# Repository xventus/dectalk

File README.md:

# DECTALK 

DECTALK is a simple application of Epson's S1V30120 chip. The communication is controlled by the ESP32 module. Esp32 provides HTTP and serial access for control. MIKROE produces a suitable module carrying the S1V30120 and an amplifier. 

The hardware directory contains a schematic and a board of plenum connections in KICAD format.
The src directory contains the source code for ESP32.

# How to use it 

The module can communicate using HTTP protocol via WiFi or using a serial link.

WiFi connection:
	- on first run, create an AP named `DECTALK CONFIG` or press reset (EN) twice within 5 seconds. 
	- web browser http://192.168.4.100 and fill in the web form

 	POST via build in fomular:  http://192.168.2.220/talk
 	POST via build in fomular:  http://192.168.2.220
	GET with url encoded string as param:   http://XXX.XXX.XXX.XXX/talk?talk=hello%20world

Serial line connection:
	- 9600.8.N.1 

LED status on the ESP32 module:
 - fast LED blinking - error, more detail after serial line
 - slow blinking LED - runs as AP `DECTALK CONFIG`
 - turns on and then off - when playing a message

# Device limitations

The message length is limited to 248 characters.

# Documentation 

S1V30120 module:  https://www.mikroe.com/text-to-speech-click.

S1V30120 initialization data: https://global.epson.com/products_and_drivers/semicon/products/speech/voice/sla/s1v30120_init_data.html

S1V30120 protocol: https://global.epson.com/products_and_drivers/semicon/pdf/id001875.pdf

# Screens

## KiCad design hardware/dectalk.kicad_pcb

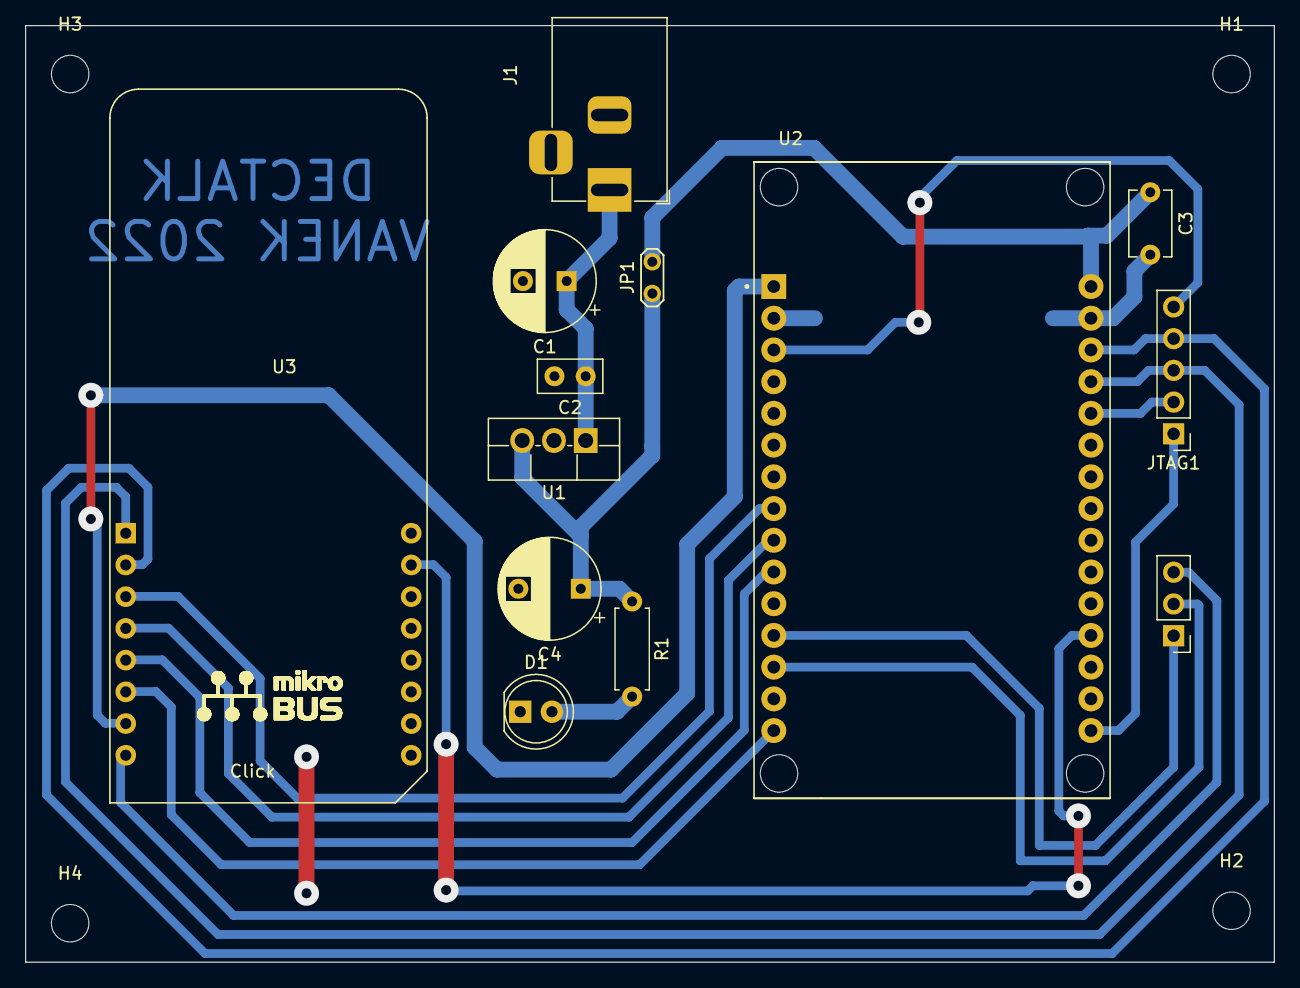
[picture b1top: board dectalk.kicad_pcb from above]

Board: 2 copper layers, 100.0 x 75.0 mm, 17 parts (0 on the bottom side), 18 nets.

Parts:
C1: 1uF; CP_Radial_D8.0mm_P3.50mm
C2: 100nF; C_Disc_D5.0mm_W2.5mm_P2.50mm
C3: 100nF; C_Disc_D5.1mm_W3.2mm_P5.00mm
C4: 10uF; CP_Radial_D8.0mm_P5.00mm
D1: LED; LED_D5.0mm_IRGrey
H1, H2, H3, H4: MountingHole; MountingHole_3mm
J1: Barrel_Jack; BarrelJack_Horizontal
J2: Conn_01x03_Female; PinHeader_1x03_P2.54mm_Vertical
JP1: power_set; TestPoint_2Pads_Pitch2.54mm_Drill0.8mm
JTAG1: Conn_01x05_Male; PinHeader_1x05_P2.54mm_Vertical
R1: 330; R_Axial_DIN0207_L6.3mm_D2.5mm_P7.62mm_Horizontal
U1: L7805; TO-220F-3_Vertical
U2: ESP32-DEVKIT-V1; MODULE_ESP32_DEVKIT_V1
U3: MIKROE-2253

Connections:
+3V3: U2.1 (3V3), U3.7 (+3.3V)
+5V: C3.1, JP1.2, U2.30 (VIN)
CS: U2.8 (D5), U3.3 (CS)
GND: C1.2, C2.2, C3.2, C4.2, D1.1 (K), J1.2, J2.3, U1.2 (GND), U2.2 (GND), U2.29 (GND), U3.8 (GND)
MUT: JTAG1.3, U2.27 (D12), U3.1 (MUT)
unnamed: C1.1, C2.1, J1.1, U1.1 (IN)
unnamed: C4.1, JP1.1, R1.1, U1.3 (OUT)
unnamed: D1.2 (A), R1.2
unnamed: J2.1, U2.12 (RX0)
unnamed: J2.2, U2.13 (TX0)
unnamed: JTAG1.5, U2.3 (D15)
unnamed: JTAG1.1, U2.16 (EN)
unnamed: JTAG1.2, U2.26 (D14)
RDY: U2.19 (D34), U3.15 (RDY)
RST: JTAG1.4, U2.28 (D13), U3.2 (RST)
SCK: U2.9 (D18), U3.4 (SCK)
SDI: U2.15 (D23), U3.6 (SDI)
SDO: U2.10 (D19), U3.5 (SDO)
